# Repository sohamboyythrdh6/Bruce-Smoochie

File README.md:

# Bruce-Smoochie

hey my name is soham karan and I am from India. i made a simmiler thing like flipper zero which can read rf tags and save it or use it later it also work same witr ir .And it just work as like flipper zero but it cheapper than flipper and you can also able to made by cheaking this repo .I made this project using esp s3 and some other components .ANd this project is powerd by a lipo battery which is charged by tp4506 charging module.
And to program the board you dont need any code insted you need a flash software which is given in my repo called firmware
and also insted of making a 3d printed case i just use the pcb to create a compact case. You just need to connect the two pcbs using Standoff Spacer Pillars.

                                             !warning! 

this project is just for education and learning purpose so please dont misuse this project.
   !!Bruce is a tool for cyber offensive and red team operations, distributed under the terms of the Affero General Public License (AGPL). It is intended for legal and authorized security testing purposes only. Use of this software for any malicious or unauthorized activities is strictly prohibited. By downloading, installing, or using Bruce, you agree to comply with all applicable laws and regulations. This software is provided free of charge, and we do not accept payments for copies or modifications. The developers of Bruce assume no liability for any misuse of the software. Use at your own risk.!!

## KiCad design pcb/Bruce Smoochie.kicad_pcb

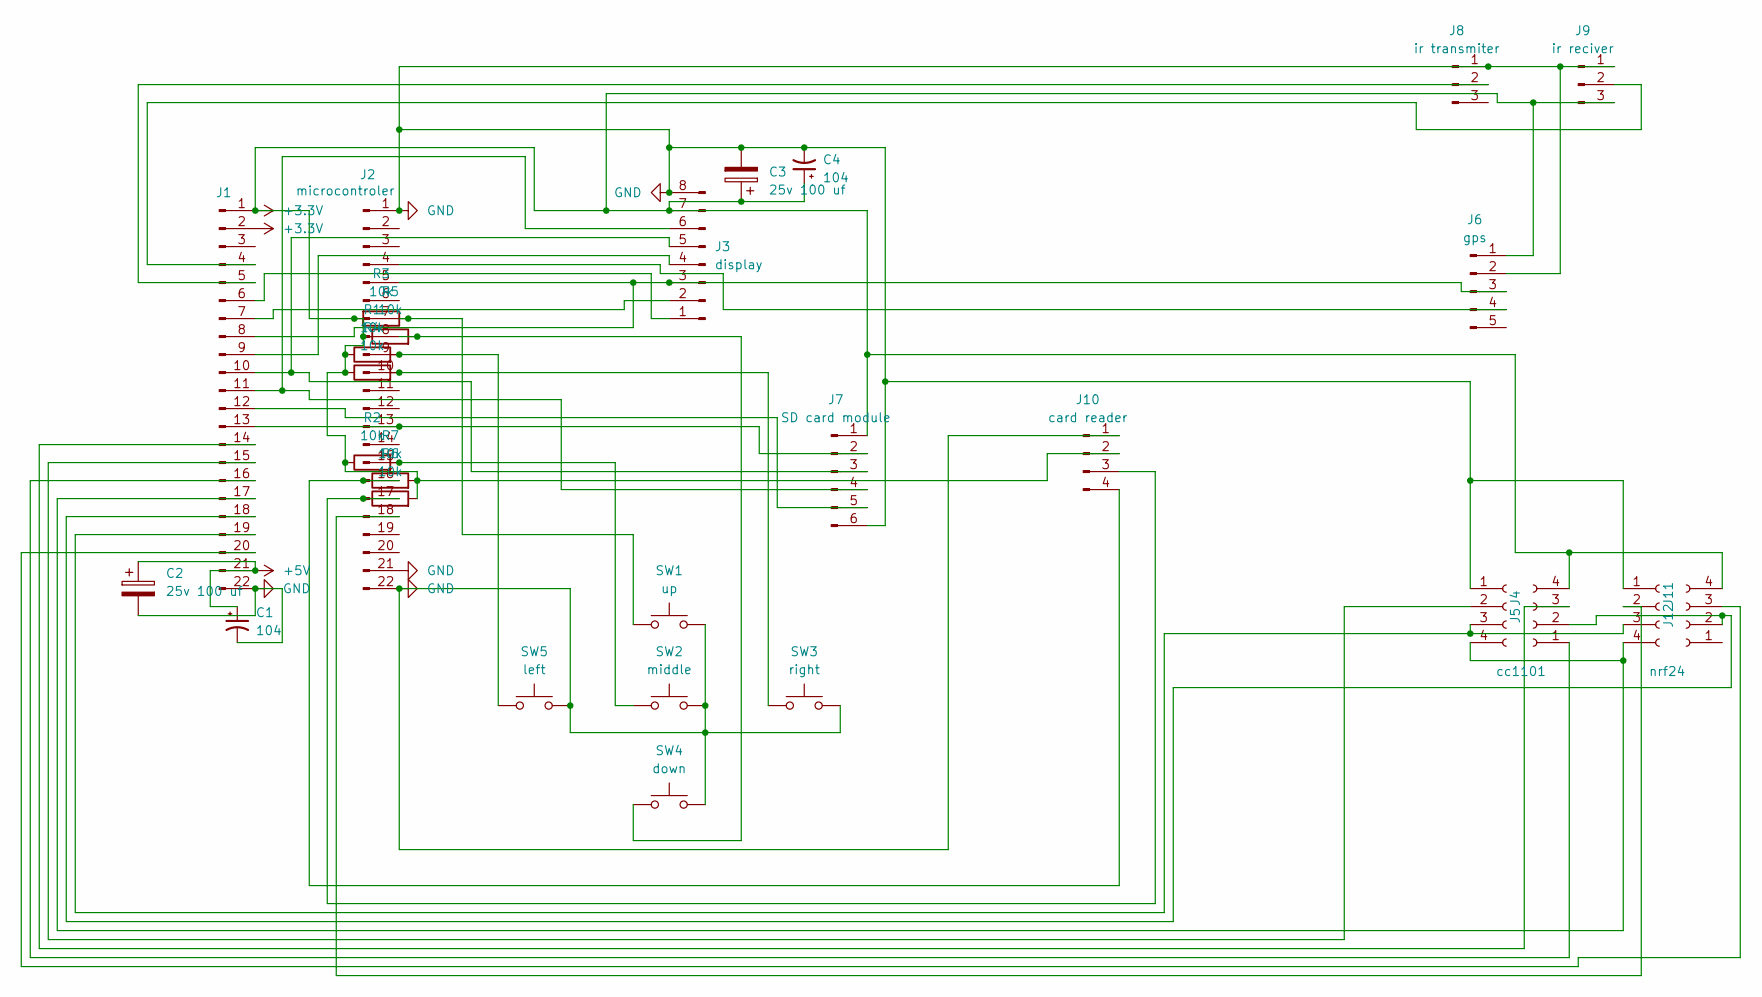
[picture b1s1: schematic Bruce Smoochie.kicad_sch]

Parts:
C1: 104; C_Disc_D3.0mm_W2.0mm_P2.50mm
C2, C3: 25v 100 uf; CP_Elec_6.3x7.7
C4: 104; C_Disc_D3.4mm_W2.1mm_P2.50mm
J1: PinSocket_1x22_P2.54mm_Vertical_SMD_Pin1Right
J2: microcontroler; PinSocket_1x22_P2.54mm_Vertical_SMD_Pin1Right
J3: display; PinSocket_1x08_P2.54mm_Vertical_SMD_Pin1Left
J4: cc1101; PinSocket_1x04_P2.54mm_Vertical
J5, J12: PinSocket_1x04_P2.54mm_Vertical
J6: gps; PinSocket_1x05_P2.54mm_Vertical
J7: SD card module; PinSocket_1x06_P2.54mm_Vertical_SMD_Pin1Right
J8: ir transmiter; PinSocket_1x03_P2.54mm_Vertical_SMD_Pin1Right
J9: ir reciver; PinSocket_1x03_P2.54mm_Vertical_SMD_Pin1Right
J10: card reader; PinSocket_1x04_P2.54mm_Vertical_SMD_Pin1Right
J11: nrf24; PinSocket_1x04_P2.54mm_Vertical
R1, R2, R3, R4, R5, R6, R7: 10k; R_1206_3216Metric_Pad1.30x1.75mm_HandSolder
SW1: up; SW_Push_1P1T_NO_CK_PTS125Sx43PSMTR
SW2: middle; SW_Push_1P1T_NO_CK_PTS125Sx43PSMTR
SW3: right; SW_Push_1P1T_NO_CK_PTS125Sx43PSMTR
SW4: down; SW_Push_1P1T_NO_CK_PTS125Sx43PSMTR
SW5: left; SW_Push_1P1T_NO_CK_PTS125Sx43PSMTR

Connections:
+3.3V: C3.1, C4.1, J1.1, J1.2, J3.7, J5.4, J6.1, J7.1, J9.3, J10.2, J12.4, R1.1, R2.1, R3.2, R4.1, R5.1, R6.2, R7.2
+5V: C1.1, C2.1, J1.21
GND: C1.2, C2.2, C3.2, C4.2, J1.22, J2.1, J2.21, J2.22, J3.8, J4.1, J6.2, J7.6, J8.1, J9.1, J10.1, J11.1, SW1.2, SW2.2, SW3.2, SW4.2, SW5.2
unnamed: J1.4, J9.2
unnamed: J1.5, J8.2
unnamed: J1.6, J3.1
unnamed: J1.7, J3.2
unnamed: J1.8, J2.5, J3.3, J6.3
unnamed: J1.9, J3.4
unnamed: J1.10, J3.5, J7.3
unnamed: J1.11, J3.6, J7.4
unnamed: J1.12, J7.5
unnamed: J1.13, J2.13, J7.2
unnamed: J1.14, J5.3
unnamed: J1.15, J4.2
unnamed: J1.16, J5.1
unnamed: J1.17, J4.4, J11.4
unnamed: J1.18, J5.2, J12.2
unnamed: J1.19, J4.3, J11.3
unnamed: J1.20, J12.3
unnamed: J2.4, J6.4
unnamed: J2.7, R3.1, SW1.1
unnamed: J2.8, R5.2, SW4.1
unnamed: J2.9, R1.2, SW5.1
unnamed: J2.10, R4.2, SW3.1
unnamed: J2.15, R2.2, SW2.1
unnamed: J2.17, J10.3, R6.1
unnamed: J2.16, J10.4, R7.1
unnamed: J2.18, J11.2

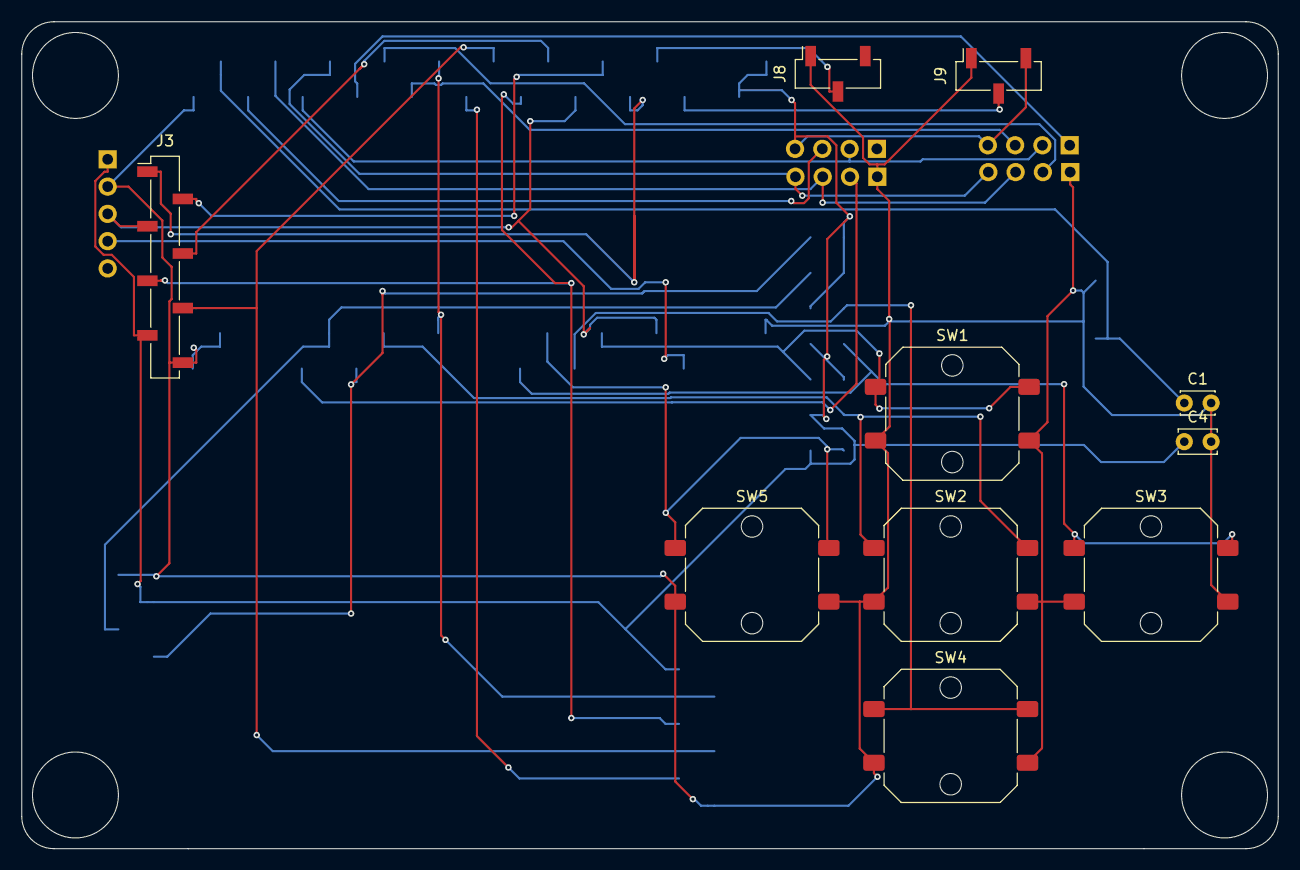
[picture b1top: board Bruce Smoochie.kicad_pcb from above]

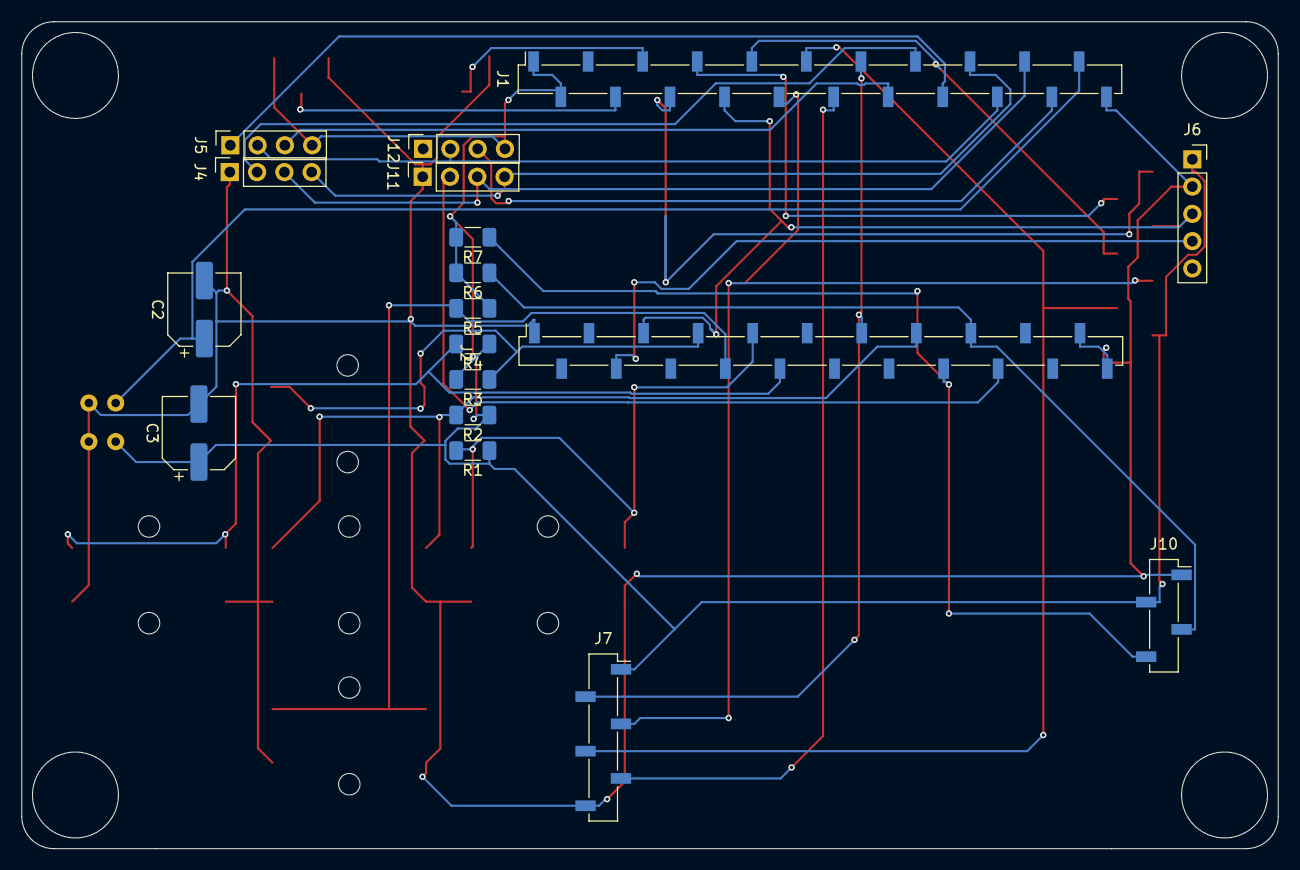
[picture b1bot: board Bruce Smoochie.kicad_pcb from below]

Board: 2 copper layers, 117.0 x 77.0 mm, 28 parts (18 on the bottom side), 29 nets.

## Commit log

2026-05-28 Update BOM.csv with new components and links
2026-05-28 Create
2026-05-29 Create j
2026-05-29 Create link
2026-06-28 Create d
2026-06-28 Create 4
